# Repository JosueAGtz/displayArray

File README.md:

# Display Array Board

The display array is a board that sets 6 ST7735 display with a resolution of 80x160px in a linear array sharing the clock, data, rs, backlight pins together, and leaving individual access to the cs lines of each display, The PCB is intended to be compatible with any Microcontroller or SBC like the Raspberry as it only needs some GPIOs and an SPI Port. This makes the PCB compatible with a simple microcontroller as an Arduino to other more advanced microcontrollers. We could say this board is a breakout board for the arrangement of six displays and 4 buttons. 

The display array has a back connector that allows the comunication with the displays and buttons. The pinout of the connector is the following:

# Display Array Clock Themes ( MY TOP 5 )

# Display Array Clock 

# Get the Display Array Board & Controller

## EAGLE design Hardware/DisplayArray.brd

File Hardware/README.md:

# Display Array Hardware

With this files you should be able to modify the board as need, also you can fabricate your own board by using the Gerber files and BOM. 

### Printed Circuit Board

### Schematic

### Display Array Board

# Display Array Controller Hardware

The controller board integrates an ESP32-S2 for its integrated USB Bootloader making it a very compact board with a powerful microcontroller with wifi and Bluetooth capabilities.

This board connects directly to the SPI Display Array Board in its back, it also has an RGB LED and Audio Amplifier for color and audible notifications. The hardware is more than capable to manage 6 displays at a decent frame rate and has enough memory for more than 5 different timezones and clock themes.

This controller has also take into account the possibility of an 8 display board and different display controller detection by the reading of one GPIO, Low logic state for ST7735, and High logic state for ST7789.

### Printed Circuit Board

### Display Array Controller Board

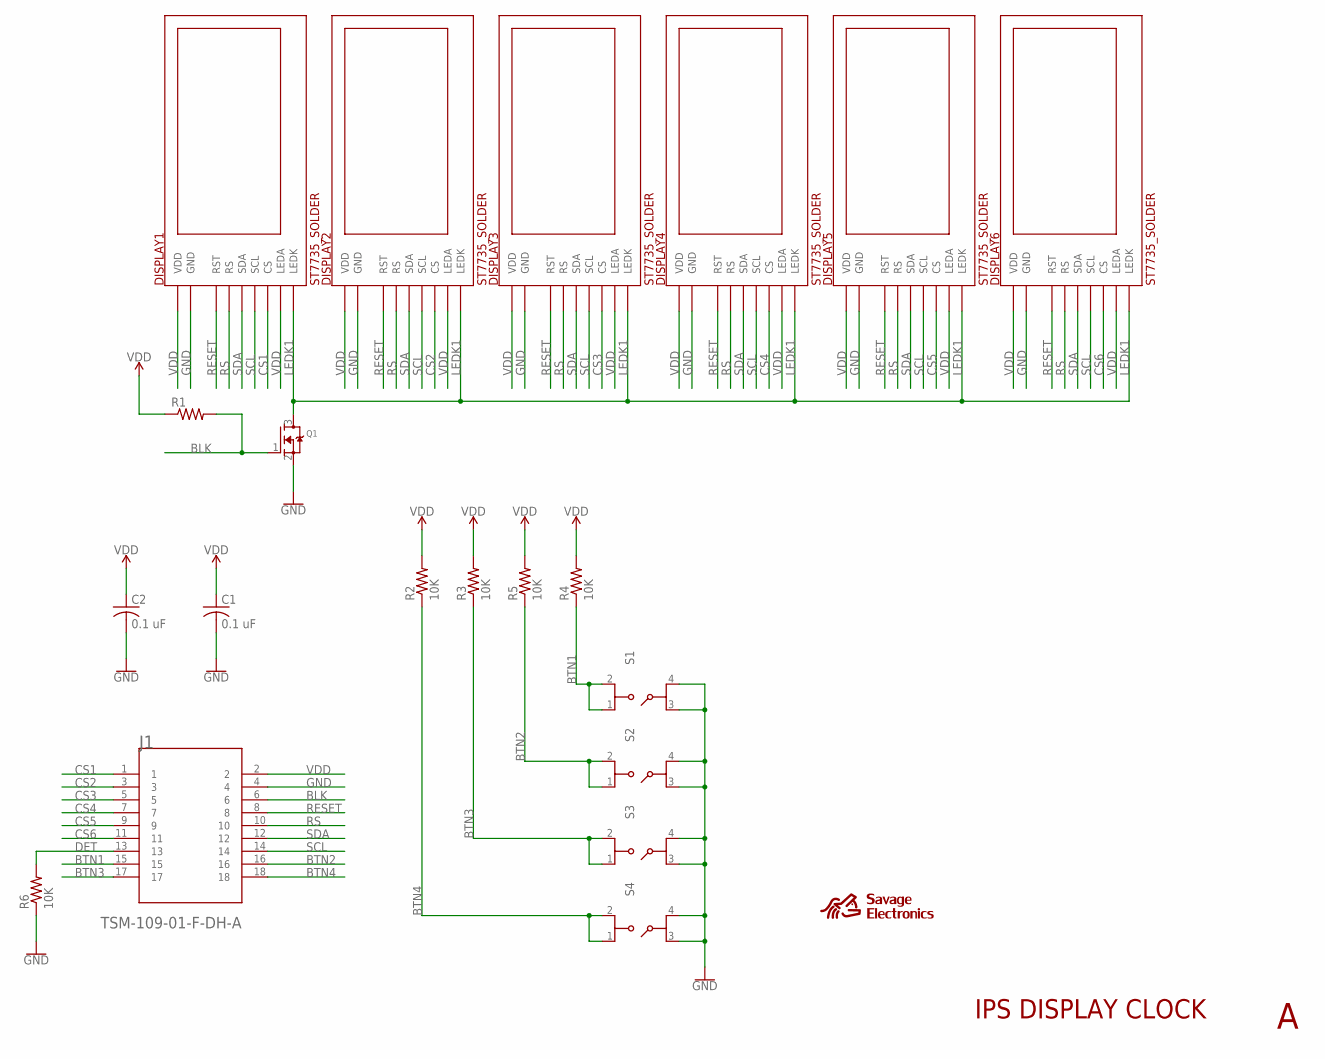
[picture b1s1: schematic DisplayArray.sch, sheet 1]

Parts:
C1, C2: 0.1 uF; C0603
DISPLAY1, DISPLAY2, DISPLAY3, DISPLAY4, DISPLAY5, DISPLAY6: ST7735_SOLDER; IPSLCD096_SOLDER
J1: TSM-109-01-F-DH-A; SAMTEC-TSM-109-02-X-DH-A
Q1: MOSFET-NREFLOW; SOT23
R1: R-US_R0805; R0805
R2, R3, R4, R5, R6: 10K; R0805
S1, S2, S3, S4: 434123025826
U$3: SE_SMALL_SILK

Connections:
BLK: J1.6, Q1.1 (G), R1.2
BTN1: J1.15, R4.1, S1.1, S1.2
BTN2: J1.16, R5.1, S2.1, S2.2
BTN3: J1.17, R3.1, S3.1, S3.2
BTN4: J1.18, R2.1, S4.1, S4.2
CS1: DISPLAY1.7 (CS), J1.1
CS2: DISPLAY2.7 (CS), J1.3
CS3: DISPLAY3.7 (CS), J1.5
CS4: DISPLAY4.7 (CS), J1.7
CS5: DISPLAY5.7 (CS), J1.9
CS6: DISPLAY6.7 (CS), J1.11
DET: J1.13, R6.2
GND: C1.2, C2.2, DISPLAY1.8 (GND), DISPLAY1.13 (GND), DISPLAY2.8 (GND), DISPLAY2.13 (GND), DISPLAY3.8 (GND), DISPLAY3.13 (GND), DISPLAY4.8 (GND), DISPLAY4.13 (GND), DISPLAY5.8 (GND), DISPLAY5.13 (GND), DISPLAY6.8 (GND), DISPLAY6.13 (GND), J1.4, Q1.2 (S), R6.1, S1.3, S1.4, S2.3, S2.4, S3.3, S3.4, S4.3, S4.4
LEDK1: DISPLAY1.11 (LEDK), DISPLAY2.11 (LEDK), DISPLAY3.11 (LEDK), DISPLAY4.11 (LEDK), DISPLAY5.11 (LEDK), DISPLAY6.11 (LEDK), Q1.3 (D)
RESET: DISPLAY1.6 (RST), DISPLAY2.6 (RST), DISPLAY3.6 (RST), DISPLAY4.6 (RST), DISPLAY5.6 (RST), DISPLAY6.6 (RST), J1.8
RS: DISPLAY1.5 (RS), DISPLAY2.5 (RS), DISPLAY3.5 (RS), DISPLAY4.5 (RS), DISPLAY5.5 (RS), DISPLAY6.5 (RS), J1.10
SCL: DISPLAY1.4 (SCL), DISPLAY2.4 (SCL), DISPLAY3.4 (SCL), DISPLAY4.4 (SCL), DISPLAY5.4 (SCL), DISPLAY6.4 (SCL), J1.14
SDA: DISPLAY1.3 (SDA), DISPLAY2.3 (SDA), DISPLAY3.3 (SDA), DISPLAY4.3 (SDA), DISPLAY5.3 (SDA), DISPLAY6.3 (SDA), J1.12
VDD: C1.1, C2.1, DISPLAY1.10 (VDD), DISPLAY1.12 (LEDA), DISPLAY2.10 (VDD), DISPLAY2.12 (LEDA), DISPLAY3.10 (VDD), DISPLAY3.12 (LEDA), DISPLAY4.10 (VDD), DISPLAY4.12 (LEDA), DISPLAY5.10 (VDD), DISPLAY5.12 (LEDA), DISPLAY6.10 (VDD), DISPLAY6.12 (LEDA), J1.2, R1.1, R2.2, R3.2, R4.2, R5.2

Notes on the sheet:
IPS DISPLAY CLOCK

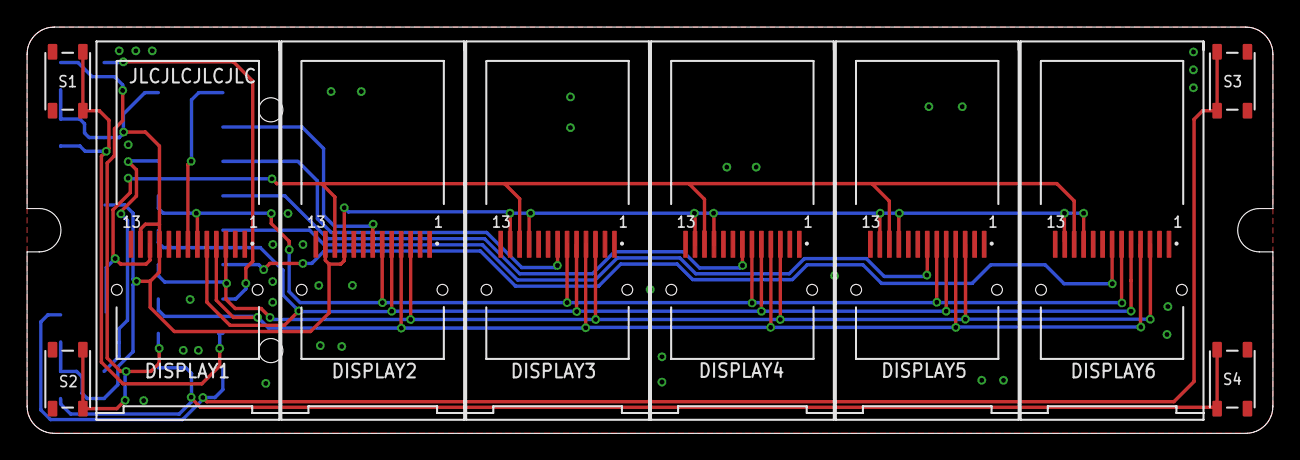
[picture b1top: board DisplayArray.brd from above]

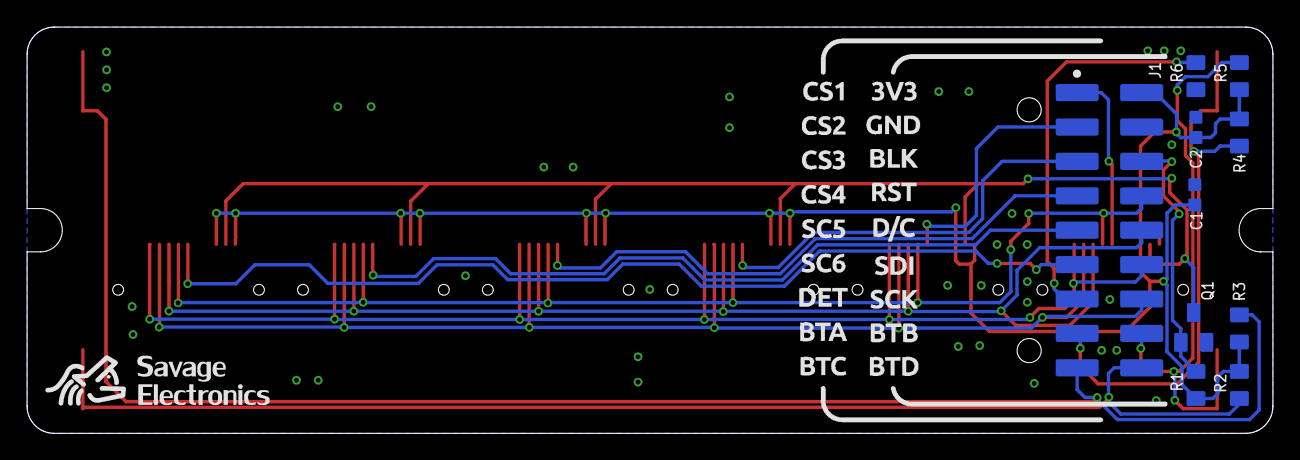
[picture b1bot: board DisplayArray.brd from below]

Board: 2 copper layers, 92.0 x 30.0 mm, 21 parts (11 on the bottom side), 19 nets.

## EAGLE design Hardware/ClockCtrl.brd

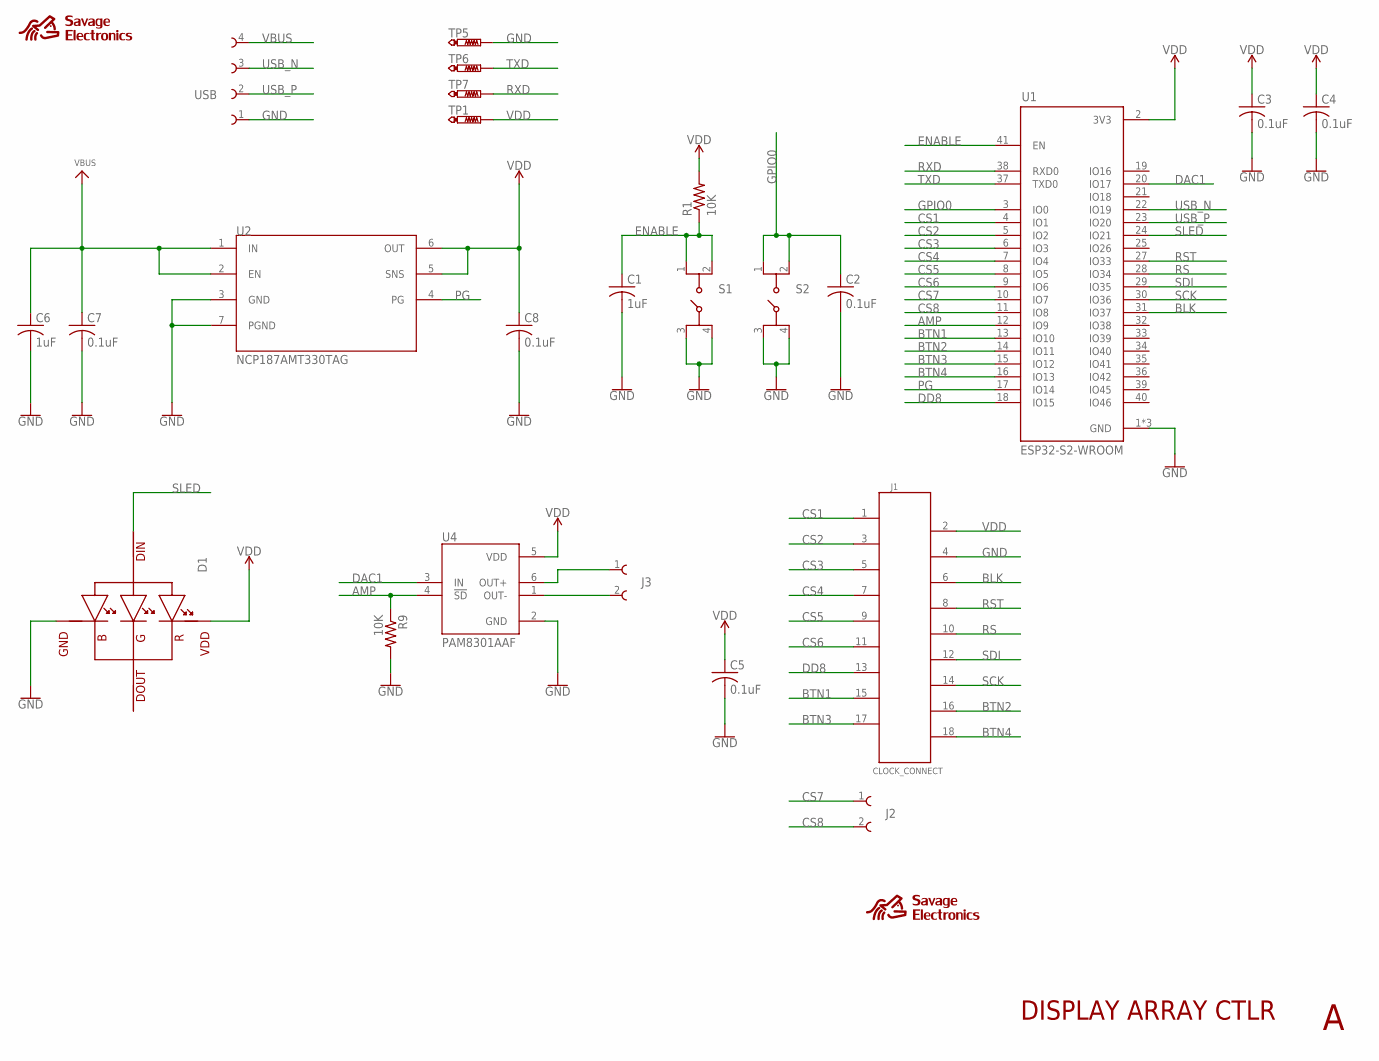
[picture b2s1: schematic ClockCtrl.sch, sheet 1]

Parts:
C1: 1uF; C0805
C2, C3, C4, C5, C7, C8: 0.1uF; C0603
C6: 1uF; C0603
D1: SK6812; 20X20
J1: CLOCK_CONNECT; CLOCKC_FOOTPRINT
J2, J3: 62000211121
R1, R9: 10K; R0603
S1, S2: 434123025826
TP1, TP5, TP6, TP7: PTR1TP12R; TP12R
U1: ESP32-S2-WROOM; XCVR_ESP32-S2-WROOM
U2: NCP187AMT330TAG; SON65P250X250X80-7N
U4: PAM8301AAF; SOT95P280X145-6N
U$1: SE_SMALL_FSILK; SE_SMALL_FACESILK
U$3: SE_SMALL_SILK
USB: 62000411121

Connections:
AMP: R9.1, U1.12 (IO9), U4.4 (!SD)
BLK: J1.6, U1.31 (IO37)
BTN1: J1.15, U1.13 (IO10)
BTN2: J1.16, U1.14 (IO11)
BTN3: J1.17, U1.15 (IO12)
BTN4: J1.18, U1.16 (IO13)
CS1: J1.1, U1.4 (IO1)
CS2: J1.3, U1.5 (IO2)
CS3: J1.5, U1.6 (IO3)
CS4: J1.7, U1.7 (IO4)
CS5: J1.9, U1.8 (IO5)
CS6: J1.11, U1.9 (IO6)
CS7: J2.1, U1.10 (IO7)
CS8: J2.2, U1.11 (IO8)
DAC1: U1.20 (IO17), U4.3 (IN)
DD8: J1.13, U1.18 (IO15)
ENABLE: C1.1, R1.1, S1.1, S1.2, U1.41 (EN)
GND: C1.2, C2.2, C3.2, C4.2, C5.2, C6.2, C7.2, C8.2, D1.3 (GND), J1.4, R9.2, S1.3, S1.4, S2.3, S2.4, TP5.TP, U1.1 (GND), U1.26 (GND), U1.42 (GND), U2.3 (GND), U2.7 (PGND), U4.2 (GND), USB.1
GPIO0: C2.1, S2.1, S2.2, U1.3 (IO0)
unnamed: J3.2, U4.1 (OUT-)
unnamed: J3.1, U4.6 (OUT+)
PG: U1.17 (IO14), U2.4 (PG)
RS: J1.10, U1.28 (IO34)
RST: J1.8, U1.27 (IO33)
RXD: TP7.TP, U1.38 (RXD0)
SCK: J1.14, U1.30 (IO36)
SDI: J1.12, U1.29 (IO35)
SLED: D1.4 (DIN), U1.24 (IO21)
TXD: TP6.TP, U1.37 (TXD0)
USB_N: U1.22 (IO19), USB.3
USB_P: U1.23 (IO20), USB.2
VBUS: C6.1, C7.1, U2.1 (IN), U2.2 (EN), USB.4
VDD: C3.1, C4.1, C5.1, C8.1, D1.1 (VDD), J1.2, R1.2, TP1.TP, U1.2 (3V3), U2.5 (SNS), U2.6 (OUT), U4.5 (VDD)

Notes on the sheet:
DISPLAY ARRAY CTLR

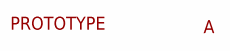
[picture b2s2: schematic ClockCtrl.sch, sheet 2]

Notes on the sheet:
PROTOTYPE

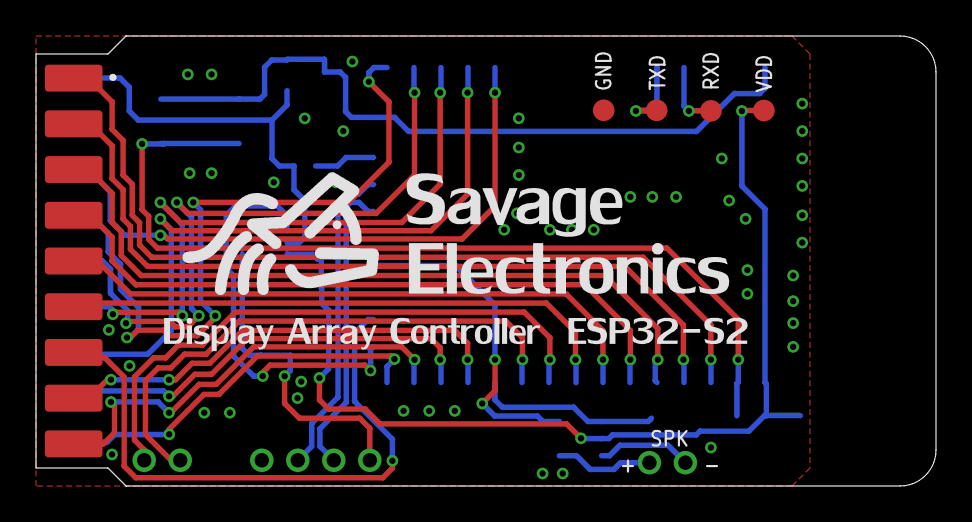
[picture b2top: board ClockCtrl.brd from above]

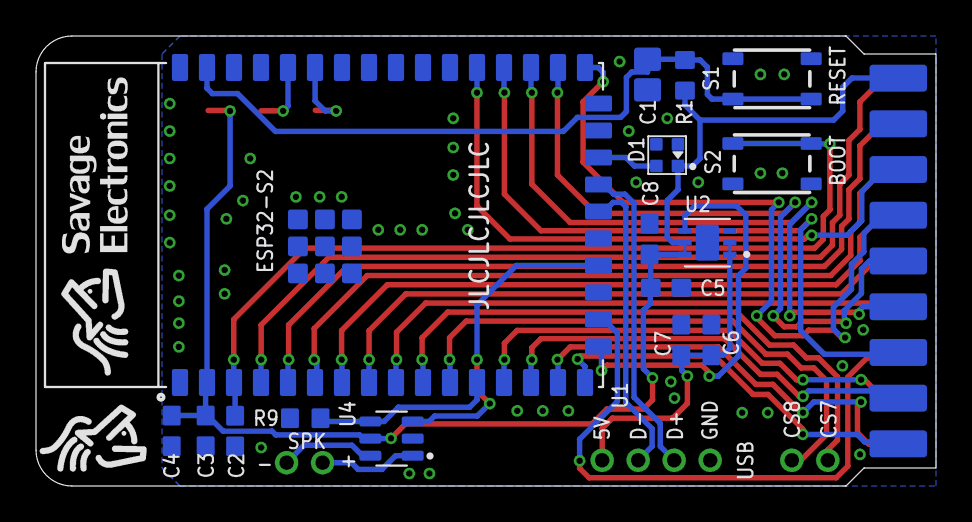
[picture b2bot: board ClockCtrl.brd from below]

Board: 2 copper layers, 50.0 x 25.0 mm, 26 parts (20 on the bottom side), 33 nets.

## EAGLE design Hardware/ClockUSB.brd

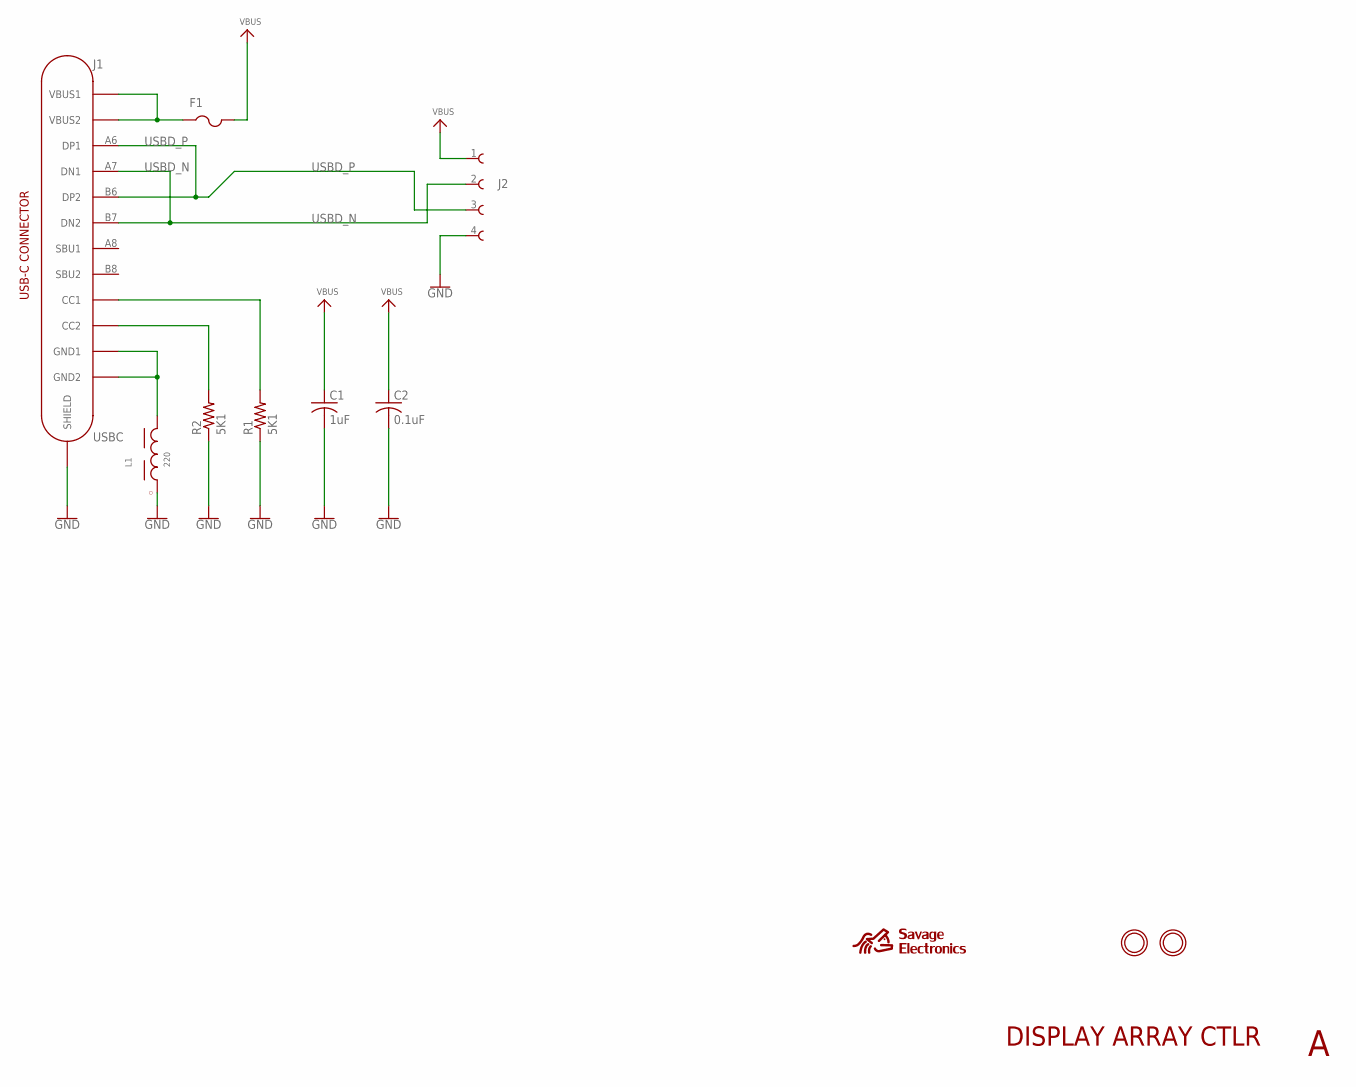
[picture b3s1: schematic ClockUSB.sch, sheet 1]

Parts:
C1: 1uF; C0603
C2: 0.1uF; C0603
F1: PTCFUSE; R0603
J1: USBC
J2: 62000411121
L1: 220; WE-CBA_0603(W=2.2)
R1, R2: 5K1; R0603
U$3: SE_SMALL_FSILK; SE_SMALL_FACESILK
U$6, U$7: MOUNTINGHOLE3.0THIN; MOUNTINGHOLE_3.0_PLATEDTHIN

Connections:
GND: C1.2, C2.2, J1.S1 (SHIELD), J1.S2 (SHIELD), J1.S3 (SHIELD), J1.S4 (SHIELD), J2.4, L1.1, R1.1, R2.1
unnamed: J1.A1B12 (GND1), J1.B1A12 (GND2), L1.2
unnamed: J1.B5 (CC2), R2.2
unnamed: J1.A5 (CC1), R1.2
unnamed: F1.1, J1.A4B9 (VBUS1), J1.B4A9 (VBUS2)
USBD_N: J1.A7 (DN1), J1.B7 (DN2), J2.2
USBD_P: J1.A6 (DP1), J1.B6 (DP2), J2.3
VBUS: C1.1, C2.1, F1.2, J2.1

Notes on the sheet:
DISPLAY ARRAY CTLR

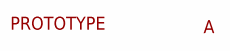
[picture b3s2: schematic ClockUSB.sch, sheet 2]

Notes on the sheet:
PROTOTYPE

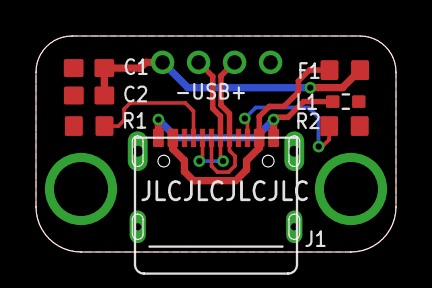
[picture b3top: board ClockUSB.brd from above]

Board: 2 copper layers, 20.0 x 12.0 mm, 11 parts (1 on the bottom side), 8 nets.

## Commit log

2021-07-05 Design Files in Autodesk Eagle
2021-07-05 Display Array Schematic - 6 Displays ST7735
2021-07-05 Media Files, display array clock themes
2021-07-06 Added Flags Master Inkscape SVG
2021-07-06 Added 14 Segment clock theme Inkscape SVG
2021-07-06 Added BINA View clock theme Inkscape SVG
2021-07-06 Added 7 Segment clock theme Inkscape SVG
2021-07-06 Added Flip Flap clock theme Inkscape SVG
2021-07-06 Added Notebook clock theme Inkscape SVG
2021-07-06 Added Lixie Cyan clock theme Inkscape SVG
2021-07-06 Added Lixie Purple clock theme Inkscape SVG
2021-07-06 Added Matrix clock theme Inkscape SVG
2021-07-06 Added NIMO clock theme Inkscape SVG
2021-07-06 Added Nixie Tube clock theme Inkscape SVG
2021-07-06 Added Pixie Pro clock theme Inkscape SVG
2021-07-06 Added VFD clock theme Inkscape SVG
2021-07-06 Added Wood clock theme Inkscape SVG
2021-07-06 Added Display Array Bill of materials
2021-07-06 Added Display Array clock firmware
2021-07-06 Visual Studio Code SNTP Clock Example

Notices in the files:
parts and their libraries:
Eagle_BOARD-TO-BOARD_CONNECTORS: Copyright: Würth Elektronik
SparkFun-PowerSymbols: Licensing: Creative Commons ShareAlike 4.0 International - https://creativecommons.org/licenses/by-sa/4.0
